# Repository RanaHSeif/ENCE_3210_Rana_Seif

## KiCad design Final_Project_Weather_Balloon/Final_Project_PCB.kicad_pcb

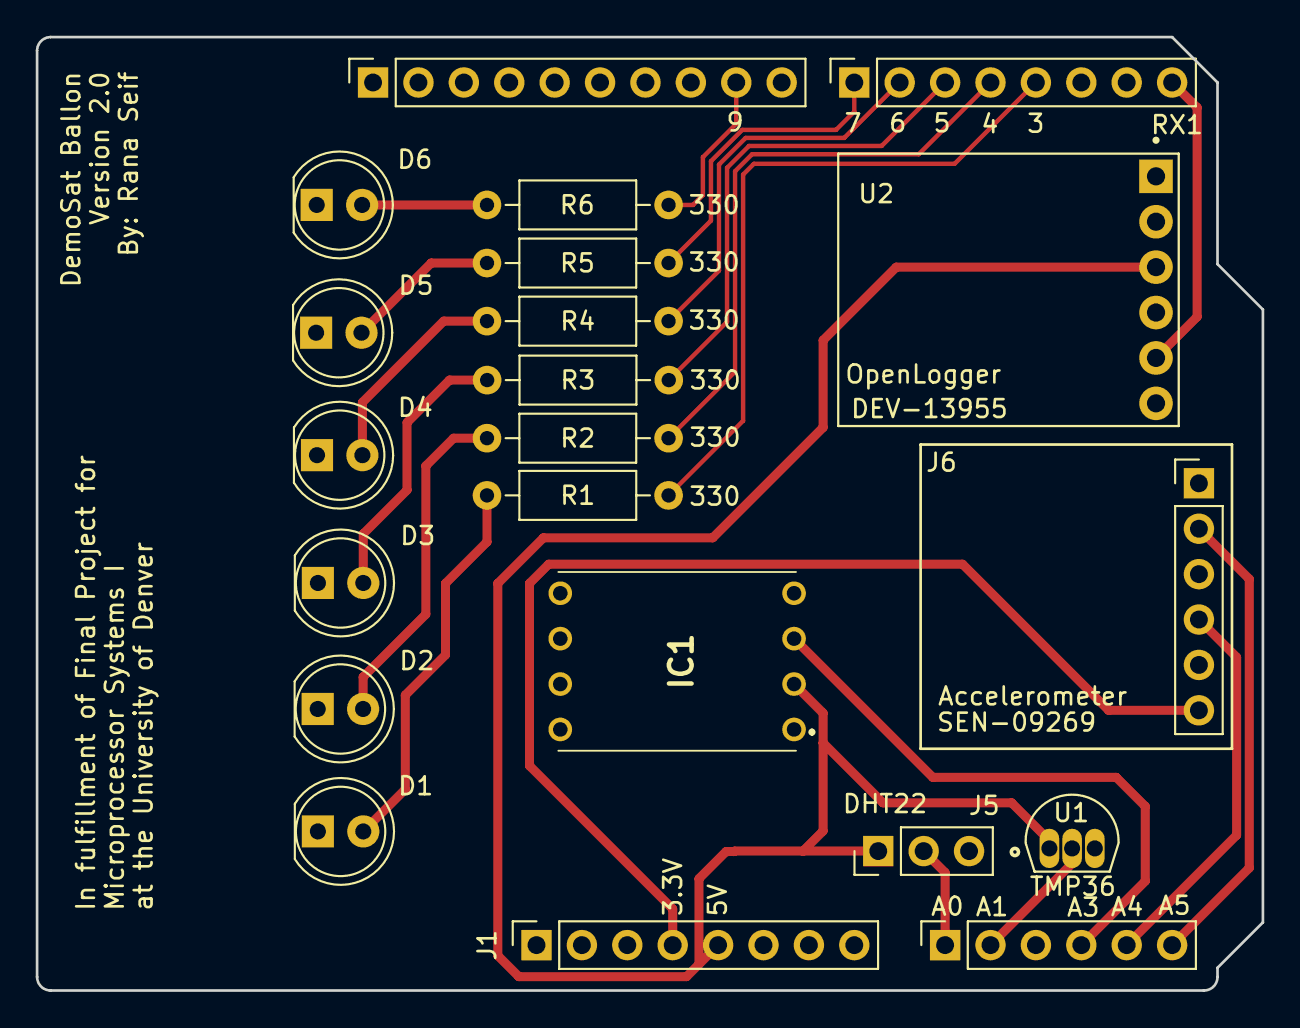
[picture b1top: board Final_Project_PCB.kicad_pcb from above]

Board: 2 copper layers, 68.6 x 53.3 mm, 21 parts (0 on the bottom side), 21 nets.

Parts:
D1: Power; LED_D5.0mm
D2: Int_Temp; LED_D5.0mm
D3: Ext_Temp; LED_D5.0mm
D4: Humidity; LED_D5.0mm
D5: Pressure; LED_D5.0mm
D6: Accelerometer; LED_D5.0mm
IC1: SSCDANV015PAAA5
J1: Power; PinSocket_1x08_P2.54mm_Vertical
J2: Digital/PWM; PinSocket_1x10_P2.54mm_Vertical
J3: Analog; PinSocket_1x06_P2.54mm_Vertical
J4: Digital/PWM; PinSocket_1x08_P2.54mm_Vertical
J5: DHT22; PinHeader_1x03_P2.54mm_Vertical
J6: Accelerometer; PinHeader_1x06_P2.54mm_Vertical
R1, R2, R3, R4, R5, R6: 330; R_Axial_DIN0207_L6.3mm_D2.5mm_P10.16mm_Horizontal
U1: TMP36; XDCR_TMP36GT9
U2: DEV-13955; MODULE_DEV-13955

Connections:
+3V3: J1.4, J6.6
+5V: IC1.2 (VSUPPLY), J1.5, J5.1, U1.1 (+VS), U2.3 (VCC)
/Accel_X: J3.5, J6.4
/Accel_Z: J3.6, J6.2
/DHT_Sensor: J3.1, J5.2
/Ext_Temp_Sensor: J3.2, U1.2 (VOUT)
/LED_Accelerometer: J2.9, R6.1
/LED_ExternalTemp: J4.3, R3.1
/LED_Humidity: J4.2, R4.1
/LED_InternalTemp: J4.4, R2.1
/LED_Power: J4.5, R1.1
/LED_Pressure: J4.1, R5.1
/Open_Logger: J4.8, U2.5 (RXI)
/Pressure_Sensor: IC1.3 (VOUT), J3.4
GND: D1.1 (K), D2.1 (K), D3.1 (K), D4.1 (K), D5.1 (K), D6.1 (K), IC1.4 (GND), J1.6, J1.7, J2.4, J5.3, J6.5, U1.3 (GND), U2.2 (GND)
unnamed: D1.2 (A), R1.2
unnamed: D2.2 (A), R2.2
unnamed: D3.2 (A), R3.2
unnamed: D4.2 (A), R4.2
unnamed: D5.2 (A), R5.2
unnamed: D6.2 (A), R6.2

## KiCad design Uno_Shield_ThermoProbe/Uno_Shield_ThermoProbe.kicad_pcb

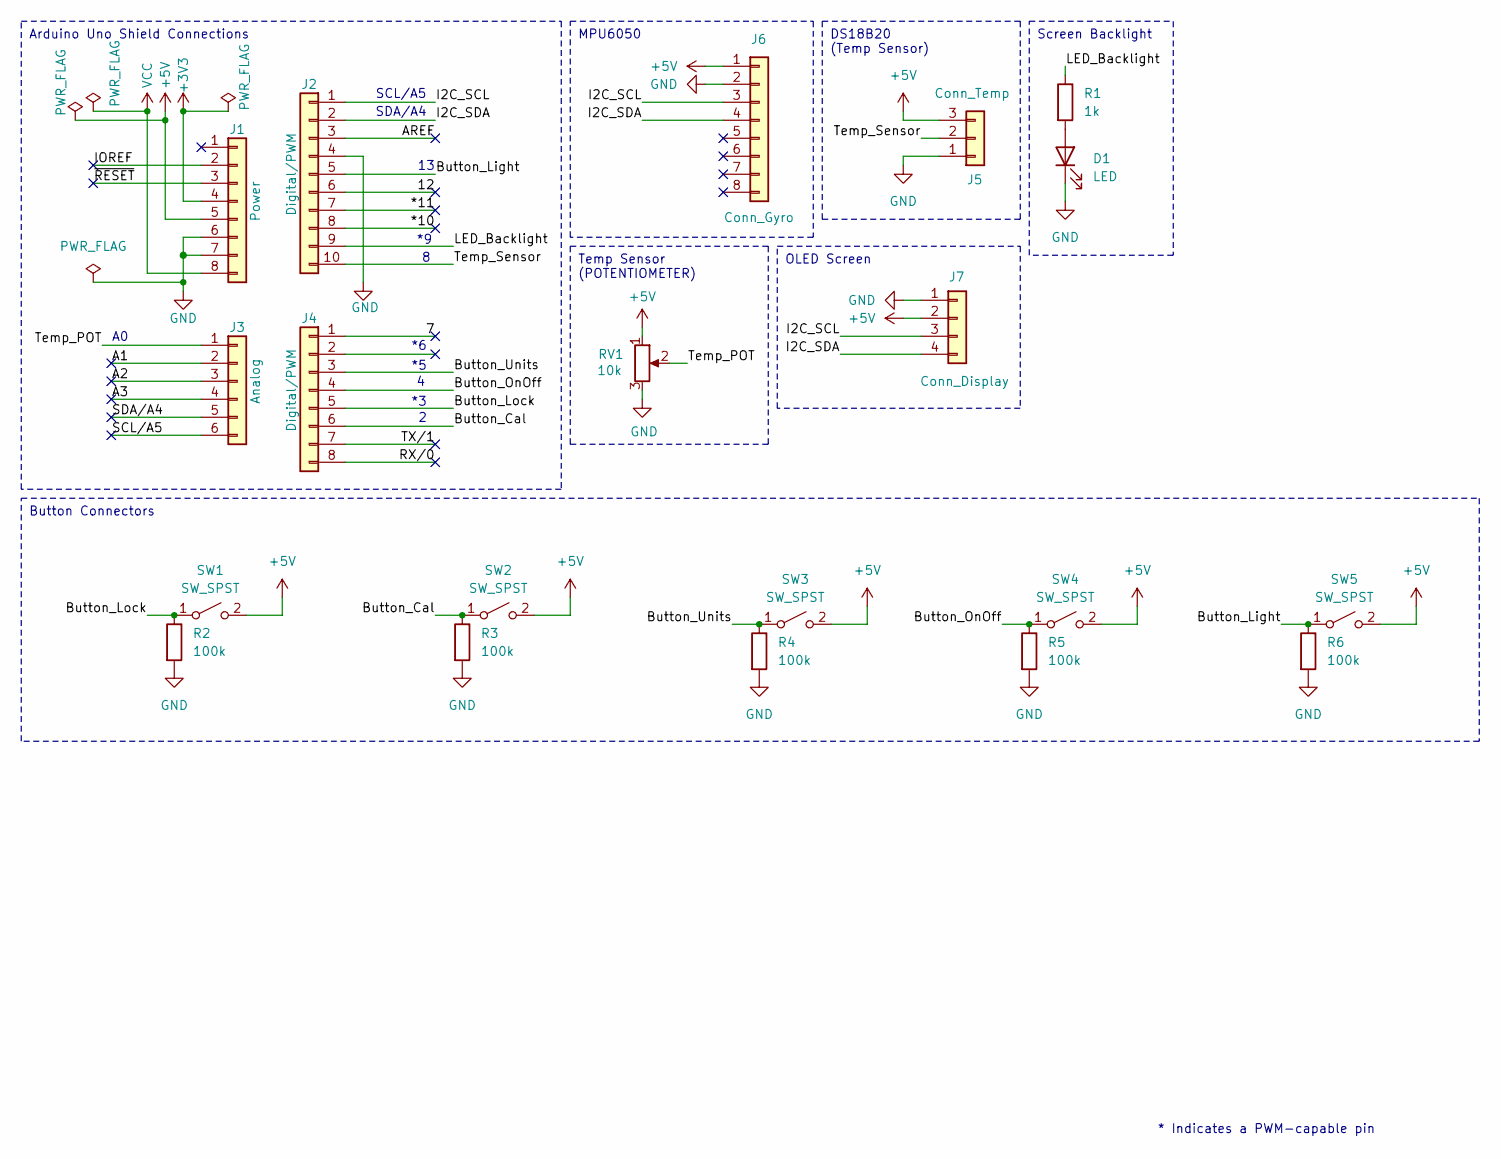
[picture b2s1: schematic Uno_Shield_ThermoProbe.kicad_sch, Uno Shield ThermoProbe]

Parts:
D1: LED; LED_D5.0mm
J1: Power; PinSocket_1x08_P2.54mm_Vertical
J2: Digital/PWM; PinSocket_1x10_P2.54mm_Vertical
J3: Analog; PinSocket_1x06_P2.54mm_Vertical
J4: Digital/PWM; PinSocket_1x08_P2.54mm_Vertical
J5: Conn_Temp; JST_XH_B3B-XH-A_1x03_P2.50mm_Vertical
J6: Conn_Gyro; PinSocket_1x08_P2.54mm_Vertical
J7: Conn_Display; PinSocket_1x04_P2.54mm_Vertical
R1: 1k; R_Axial_DIN0207_L6.3mm_D2.5mm_P10.16mm_Horizontal
R2, R3, R4, R5, R6: 100k; R_Axial_DIN0207_L6.3mm_D2.5mm_P10.16mm_Horizontal
RV1: 10k; Potentiometer_Bourns_3386P_Vertical
SW1, SW2, SW3, SW4, SW5: SW_SPST; SW_PUSH_6mm

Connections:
+3V3: J1.4
+5V: J1.5, J5.3, J6.1, J7.2, RV1.1, SW1.2 (B), SW2.2 (B), SW3.2 (B), SW4.2 (B), SW5.2 (B)
/7: J4.1
/12: J2.6
/*10: J2.8
/*11: J2.7
/A1: J3.2
/A2: J3.3
/A3: J3.4
/AREF: J2.3
/Button_Cal: J4.6, R3.1, SW2.1 (A)
/Button_Light: J2.5, R6.1, SW5.1 (A)
/Button_Lock: J4.5, R2.1, SW1.1 (A)
/Button_OnOff: J4.4, R5.1, SW4.1 (A)
/Button_Units: J4.3, R4.1, SW3.1 (A)
/I2C_SCL: J2.1, J6.3, J7.3
/I2C_SDA: J2.2, J6.4, J7.4
/IOREF: J1.2
/LED_Backlight: J2.9, R1.1
/RX/0: J4.8
/SCL/A5: J3.6
/SDA/A4: J3.5
/TX/1: J4.7
/Temp_POT: J3.1, RV1.2
/Temp_Sensor: J2.10, J5.2
/~RESET: J1.3
GND: D1.1 (K), J1.6, J1.7, J2.4, J5.1, J6.2, J7.1, R2.2, R3.2, R4.2, R5.2, R6.2, RV1.3
unnamed: D1.2 (A), R1.2
VCC: J1.8

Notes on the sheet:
Temp Sensor (POTENTIOMETER)
Screen Backlight
DS18B20 (Temp Sensor)
Button Connectors
Arduino Uno Shield Connections
OLED Screen
MPU6050
SCL/A5
SDA/A4
* Indicates a PWM-capable pin

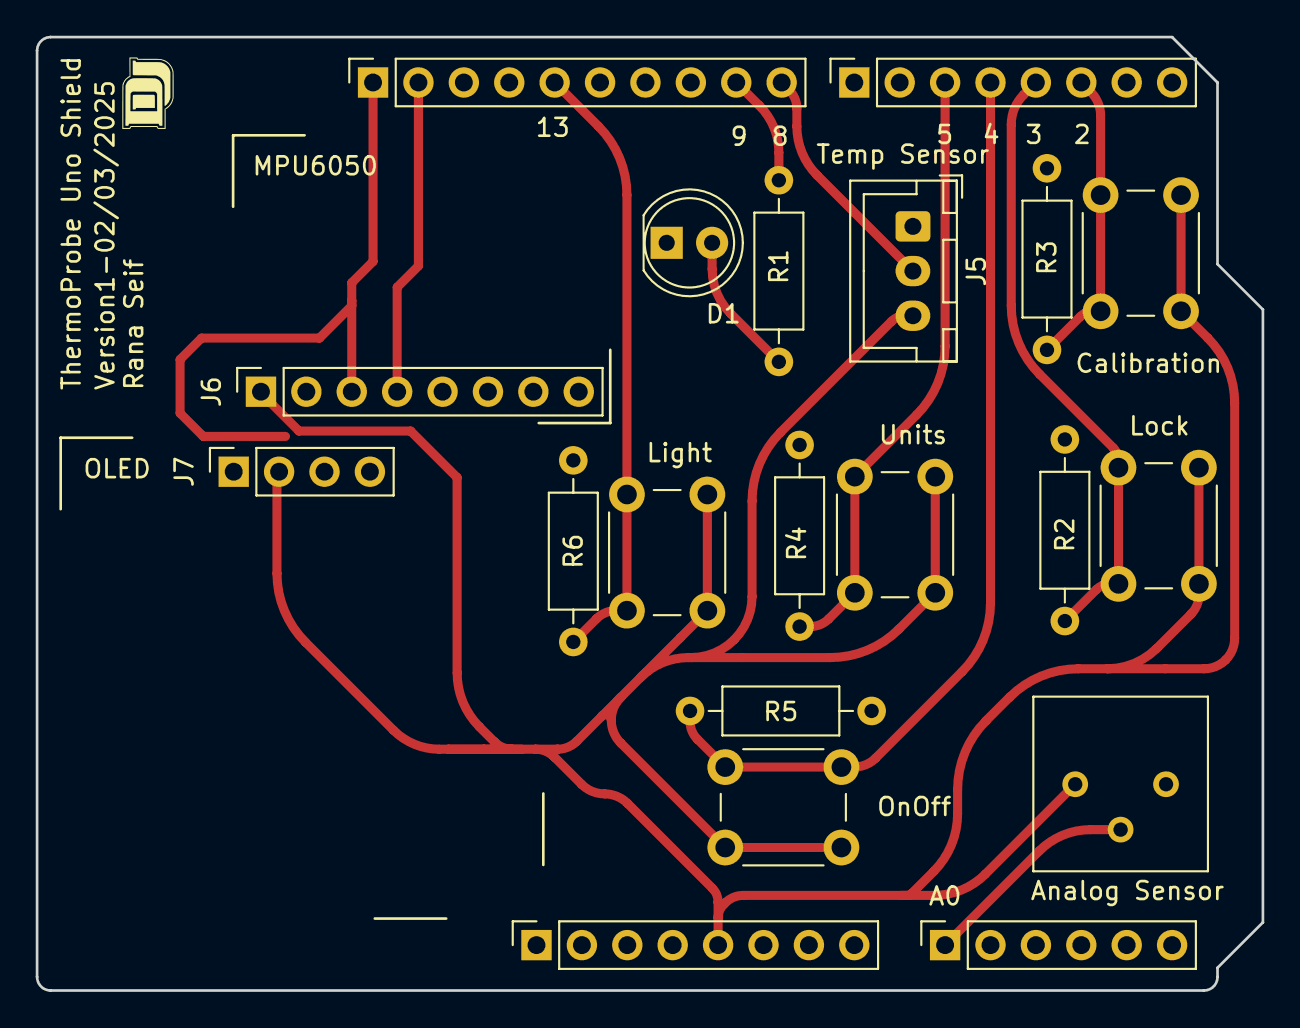
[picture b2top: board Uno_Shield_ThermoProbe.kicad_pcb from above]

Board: 2 copper layers, 68.6 x 53.3 mm, 20 parts (0 on the bottom side), 13 nets.

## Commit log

2025-01-10 Lab1 Project 2
2025-01-17 Lab1 (Problems 1 through 7) in C Code Using Arduino IDE and Arduino Uno Microprocessor.
2025-01-24 Problem Files for Lab 2 of Microprocessor Systems I
2025-01-31 Lab3 Documents (Timer Interrupts)
2025-01-31 Lab3_Code.ino
2025-02-03 Folder with all files for ThermoProbe Uno Shield PCB Design.
2025-02-03 ThermoProbe PCB Files
2025-02-04 Deleted Files
2025-02-04 Files for ThermoProbe PCB V1 02/03/2025
2025-02-04 Changes made, so files were replaced
2025-02-04 ThermoProbe PCB Files V2 02/02/2025
2025-02-26 Uno_Shield_ThermoProbe updated Folder with Code
2025-03-04 Microprocessors Lab 4 Code Files V1 Rana Seif - 3/3/2025
2025-03-05 Slight Changes
2025-03-05 V2 (Slight Changes to comments)
2025-03-07 Lab 4 Problems 1 and 4 V2. Slight Changes
    In Problem 1, only comment changes.
    In Problem 4, PWM timer was added.
2025-03-07 Block diagrams for Lab 4 problems 2 through 4 (2 and 3 are combined).
2025-03-07 ThermoProbe Code by Rana Seif
2025-03-07 ThermoProbe Code V2 Date: 3/7/2025 Some slight changes were made to the code. It now all works except for the units button.
2025-03-14 Final Project Weather Balloon V1 By Rana Seif 3/13/2025
